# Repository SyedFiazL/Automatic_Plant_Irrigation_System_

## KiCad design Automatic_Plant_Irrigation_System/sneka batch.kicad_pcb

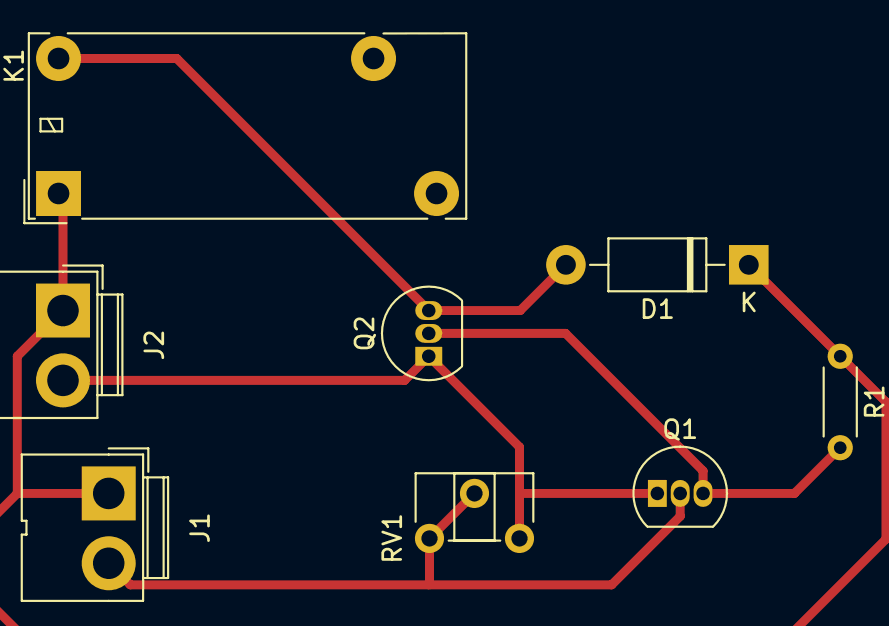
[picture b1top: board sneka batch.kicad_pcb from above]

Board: 2 copper layers, 8 parts (0 on the bottom side), 5 nets.

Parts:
D1: 1N4007; D_DO-41_SOD81_P10.16mm_Horizontal
J1: connector; JWT_A3963_1x02_P3.96mm_Vertical
J2: Screw_Terminal_01x02; JWT_A3963_1x02_P3.96mm_Vertical
K1: ADW11; Relay_1P1T_NO_10x24x18.8mm_Panasonic_ADW11xxxxW_THT
Q1, Q2: 2N3904; TO-92_Inline
R1: 1k; R_Axial_DIN0204_L3.6mm_D1.6mm_P5.08mm_Horizontal
RV1: 50k; Potentiometer_ACP_CA6-H2,5_Horizontal

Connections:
unnamed: D1.1 (K), J1.1, J2.1, K1.1, R1.1
unnamed: D1.2 (A), K1.6, Q2.3 (C)
unnamed: J1.2, Q1.2 (B), RV1.1, RV1.2
unnamed: J2.2, Q1.1 (E), Q2.1 (E), RV1.3
unnamed: Q1.3 (C), Q2.2 (B), R1.2
